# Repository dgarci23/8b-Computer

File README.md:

# 8-b Computer
8 bit Computer design based on Ben Eater's 8 Bit Computer Youtube series. Hardware implementation of the design, KiCad schematics and Verilog implementation.

The project consists of three parts:
- Hardware implementation of an 8 bit computer using TTL chips and breadboards following Ben Eater's design.
- Schematics and documentation for the hardware design in KiCad.
- FPGA implementation in an Altera DE2-115 using Verilog and Quartus.

# Hardware Design
Below is the final design of the breadboard implementation of the 8 bit Computer. 

### Modules
The breadboard implementation consists of:
- **Clock Module**: allows the user to work with an automatic clock with changeable frequency or a manual clock for debugging.
- **Memory Module**: 16 memory addresses of 8 bits each form the memory of the 8 bit computer. Both instructions and data are stored in the same memory. Manual memory programing is implemented.
- **Registers**: there are three registers implemented in the breadboard. Register A and B that hold data and the Instruction Register that holds the value of the current instruction.
- **ALU**: the ALU is able to implement addition and substraction of register A and B.
- **Program Counter**: the program counter keeps the value of the current instruction address.
- **Output Module**: the output module allows the user to see the results of the execution using 8 segment displays.
- **Control Unit**: using Flash Memories as "look-up tables" to keep the relationship between instructions and control signals, the Control Unit consists of the control signals that are sent into the different modules of the computer and the Flags Registers that allow for branch operations to work.

### ISA
The instruction set architecture for the computer is a custom made ISA for this specific implementation. 
It includes:
- A load immediate for Register A.
- A load and store functions for memory.
- Arithmetic functions add and substract.
- Jump instructions including simple jump, jump if zero and jump if carry.
- Output instruction to display on the 8 segment display.
- Halt instruction to stop execution.

### Power distribution and issues
Power distribution was a big challenge to make the computer work. Extensive connection between multiple ground and power lines was necessary to avoid high voltage differences across the computer that was creating bugs in the registers and the bus. Breadboard connections quality was also a problem, since some connections were not smooth and some chips disconnected from its breadboard creating bugs.

For the kiCad schematics of the implementation: [Click here](https://github.com/dgarci23/8b-Computer/blob/main/8'b%20Computer%20Schematics/Plot/8'b%20Computer.pdf)

# FPGA Implementation using Verilog
Using an Altera DE2-115 FPGA, I translated the breadboard implementation to a Verilog model and uploaded it to the FPGA using Quartus. Some minor changes were made from the Breadboard implementation, but the main functionality and ISA stayed the same. 

To improve program writing and loading into the FPGA, I developed a Serial terminal on PyGame to write and send programs to the FPGA via a USB-Serial cable and by implementing a program loader using Serial in the FPGA. 

The biggest challenges were to setup the serial communication in the FPGA in a way that it could detect where a program started. This was done by creating a "starting" sequence of two empty instructions (0x00) in a row, after that the actual program was fetched.

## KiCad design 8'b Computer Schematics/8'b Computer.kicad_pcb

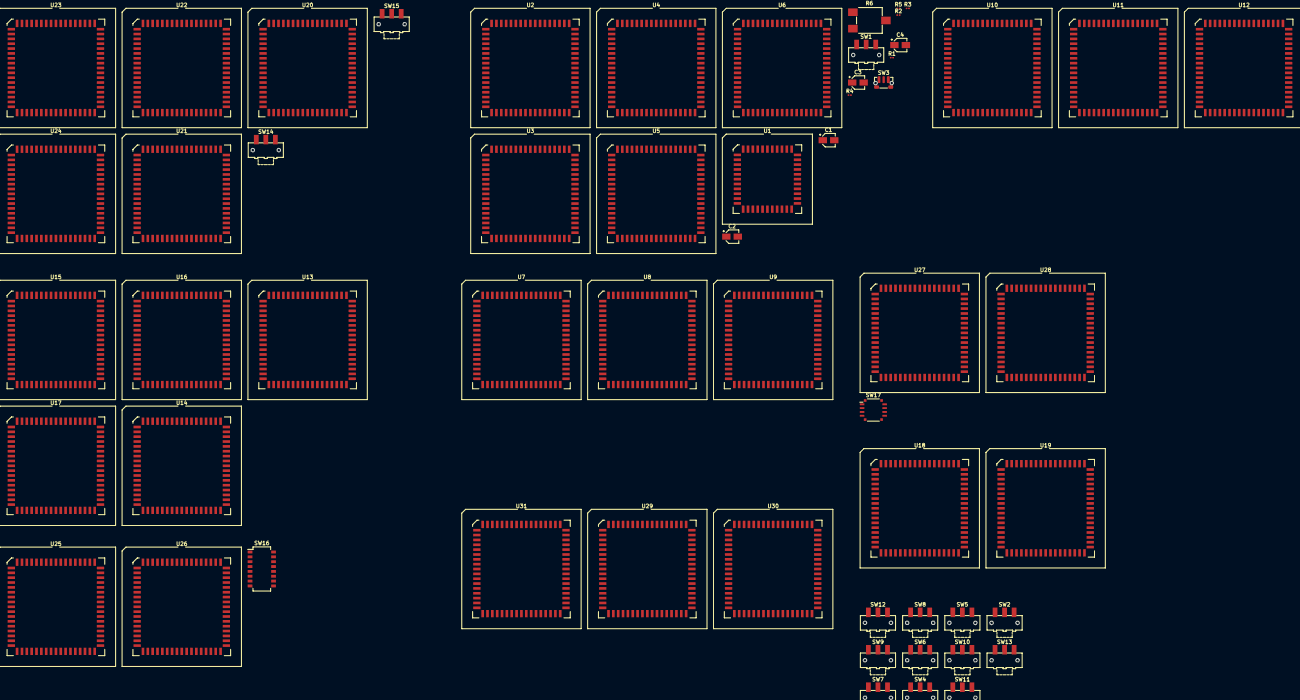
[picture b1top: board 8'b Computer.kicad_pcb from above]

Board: 2 copper layers, 58 parts (0 on the bottom side), 114 nets, no tracks yet.

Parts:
C1, C2, C4: 100p; CP_Elec_3x5.3
C3: 3.3u; CP_Elec_3x5.3
R1, R2, R3: 1k; R_0201_0603Metric
R4: 1M; R_0201_0603Metric
R5: 10k; R_0201_0603Metric
R6: 10k pot; Potentiometer_ACP_CA6-VSMD_Vertical
SW1, SW2, SW4, SW5, SW6, SW7, SW8, SW9, SW10, SW11, SW12, SW13, SW14: SW_SPDT; SW_SPDT_CK-JS102011SAQN
SW3: SW_Push; SW_Push_1P1T-MP_NO_Horizontal_Alps_SKRTLAE010
SW15: SW_Push; SW_SPDT_CK-JS102011SAQN
SW16: SW_DIP_x08; SW_DIP_SPSTx08_Slide_Omron_A6H-8101_W6.15mm_P1.27mm
SW17: SW_DIP_x04; SW_DIP_SPSTx04_Slide_Copal_CVS-04xB_W5.9mm_P1mm
U1: 74LS04; PLCC-44_SMD-Socket
U2, U5, U6: LM5550N; PLCC-68_SMD-Socket
U3: 74LS08; PLCC-68_SMD-Socket
U4: 74LS32; PLCC-68_SMD-Socket
U7, U10, U14, U18, U21, U23, U29: 74LS245; PLCC-68_SMD-Socket
U8, U9, U11, U12, U27, U30, U31: 74LS173; PLCC-68_SMD-Socket
U13, U16: 74LS86; PLCC-68_SMD-Socket
U15, U17: 74LS283; PLCC-68_SMD-Socket
U19: 74LS161; PLCC-68_SMD-Socket
U20: 74LS00; PLCC-68_SMD-Socket
U22, U25, U26, U28: 74LS157; PLCC-68_SMD-Socket
U24: AS6C62256; PLCC-68_SMD-Socket

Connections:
/ALU/SUB: SW10.2, U13.2, U13.5, U13.10, U13.13, U16.2, U16.5, U16.10, U16.13
/ALU/carry: U15.9, U17.7
/ALU/e0: U14.2, U15.4
/ALU/e1: U14.3, U15.1
/ALU/e2: U14.4, U15.13
/ALU/e3: U14.5, U15.10
/ALU/e4: U14.6, U17.4
/ALU/e5: U14.7, U17.1
/ALU/e6: U14.8, U17.13
/ALU/e7: U14.9, U17.10
/ALU/~EO: SW9.2, U14.19
/Clock/ASTABLE: U3.2, U6.3
/Clock/CoupleC: C1.1, U2.5
/Clock/HLT: SW2.2, U1.1
/Clock/MONOSTABLE: U3.4, U5.3
/Clock/SELECTOR: U1.3, U2.3, U3.5
/Instruction Register/inst4: U29.6, U31.3
/Instruction Register/inst5: U29.7, U31.4
/Instruction Register/inst6: U29.8, U31.5
/Instruction Register/inst7: U29.9, U31.6
/Instruction Register/~II: U30.9, U30.10, U31.9, U31.10
/Memory/Memory Address/MI: U27.9, U27.10
/Memory/Memory Address/manual0: SW17.1, U28.2
/Memory/Memory Address/manual1: SW17.2, U28.5
/Memory/Memory Address/manual2: SW17.3, U28.11
/Memory/Memory Address/manual3: SW17.4, U28.14
/Memory/Memory Address/mux_s: U22.1, U28.1
/Memory/Memory Values/manual0: SW16.8, U25.2
/Memory/Memory Values/manual1: SW16.7, U25.5
/Memory/Memory Values/manual2: SW16.6, U25.11
/Memory/Memory Values/manual3: SW16.5, U25.14
/Memory/Memory Values/manual4: SW16.4, U26.2
/Memory/Memory Values/manual5: SW16.3, U26.5
/Memory/Memory Values/manual6: SW16.2, U26.11
/Memory/Memory Values/manual7: SW16.1, U26.14
/Memory/Memory Values/mux_s: SW14.2, U25.1, U26.1
/Memory/WE: U20.2, U20.5
/Memory/inner0: U21.2, U23.2, U24.11
/Memory/inner1: U21.3, U23.3, U24.12
/Memory/inner2: U21.4, U23.4, U24.13
/Memory/inner3: U21.5, U23.5, U24.15
/Memory/inner4: U21.6, U23.6, U24.16
/Memory/inner5: U21.7, U23.7, U24.17
/Memory/inner6: U21.8, U23.8, U24.18
/Memory/inner7: U21.9, U23.9, U24.19
/Memory/~OE: U20.4, U21.19, U23.19, U24.22
/Program Counter/CE: SW12.2, U19.7, U19.10
/Program Counter/pc0: U18.14, U19.14
/Program Counter/pc1: U18.13, U19.13
/Program Counter/pc2: U18.12, U19.12
/Program Counter/pc3: U18.11, U19.11
/Program Counter/~CO: SW11.2, U18.19
/Program Counter/~J: SW13.2, U19.9
/RegisterA/a0: U7.2, U8.3
/RegisterA/a1: U7.3, U8.4
/RegisterA/a2: U7.4, U8.5
/RegisterA/a3: U7.5, U8.6
/RegisterA/a4: U7.6, U9.3
/RegisterA/a5: U7.7, U9.4
/RegisterA/a6: U7.8, U9.5
/RegisterA/a7: U7.9, U9.6
/RegisterA/~AI: SW4.2, U8.9, U8.10, U9.9, U9.10
/RegisterA/~AO: SW5.2, U7.19
/RegisterB/b0: U10.2, U11.3
/RegisterB/b1: U10.3, U11.4
/RegisterB/b2: U10.4, U11.5
/RegisterB/b3: U10.5, U11.6
/RegisterB/b4: U10.6, U12.3
/RegisterB/b5: U10.7, U12.4
/RegisterB/b6: U10.8, U12.5
/RegisterB/b7: U10.9, U12.6
/RegisterB/~BI: SW6.2, U11.9, U11.10, U12.9, U12.10
/RegisterB/~BO: SW7.2, U10.19
CLK: U3.8, U8.7, U9.7, U11.7, U12.7, U19.2, U20.1, U27.7, U30.7, U31.7
GND: C1.2, C2.1, C3.2, C4.1, SW1.2, SW2.1, SW3.1, SW4.1, SW5.1, SW6.1, SW7.1, SW8.1, SW9.1, SW10.1, SW11.1, SW12.1, SW13.1, SW14.1, SW15.1, SW16.9, SW16.10, SW16.11, SW16.12, SW16.13, SW16.14, SW16.15, SW16.16, SW17.5, SW17.6, SW17.7, SW17.8, U1.7, U2.1, U2.6, U2.7, U3.7, U4.7, U5.1, U6.1, U7.10, U8.1, U8.2, U8.8, U9.1, U9.2, U9.8, U10.10, U11.1, U11.2, U11.8, U12.1, U12.2, U12.8, U13.7, U14.10, U15.7, U15.8, U16.7, U17.8, U18.1, U18.2, U18.3, U18.4, U18.5, U18.10, U18.15, U18.16, U18.17, U18.18, U19.8, U20.7, U21.10, U22.8, U22.15, U23.10, U24.1, U24.2, U24.3, U24.4, U24.5, U24.6, U24.14, U24.20, U24.21, U24.23, U24.24, U24.25, U24.26, U25.8, U25.15, U26.8, U26.15, U27.1, U27.2, U27.8, U28.8, U28.15, U29.2, U29.3, U29.4, U29.5, U29.10, U30.1, U30.2, U30.8, U31.1, U31.2, U31.8
unnamed: C2.2, U5.5
unnamed: C3.1, R4.2, U5.6, U5.7
unnamed: C4.2, U6.5
unnamed: R1.2, SW1.1, U2.2
unnamed: R2.1, SW1.3, U2.4
unnamed: R3.2, SW3.2, U5.2
unnamed: R5.1, R6.2
unnamed: R5.2, U6.7
unnamed: R6.1, U6.2, U6.6
unnamed: SW15.2, U22.2
unnamed: U1.2, U3.10
unnamed: U1.4, U3.1
unnamed: U3.3, U4.2
unnamed: U3.6, U4.1
unnamed: U3.9, U4.3
unnamed: U13.3, U15.6
unnamed: U13.6, U15.2
unnamed: U13.8, U15.15
unnamed: U13.11, U15.11
unnamed: U16.3, U17.6
unnamed: U16.6, U17.2
unnamed: U16.8, U17.15
unnamed: U16.11, U17.11
unnamed: U20.3, U22.3
unnamed: U20.6, U21.1
unnamed: U27.3, U28.3
unnamed: U27.4, U28.6
unnamed: U27.5, U28.10
unnamed: U27.6, U28.13
PWR: R1.1, R2.2, R3.1, R4.1, SW2.3, SW4.3, SW5.3, SW6.3, SW7.3, SW8.3, SW9.3, SW10.3, SW11.3, SW12.3, SW13.3, SW14.3, U1.14, U2.8, U3.14, U4.14, U5.4, U5.8, U6.4, U6.8, U7.1, U7.20, U8.16, U9.16, U10.1, U10.20, U11.16, U12.16, U13.14, U14.1, U14.20, U15.16, U16.14, U17.16, U18.20, U19.16, U20.14, U21.20, U22.16, U23.1, U23.20, U24.28, U25.16, U26.16, U27.16, U28.16, U29.1, U29.20, U30.16, U31.16
bus0: U7.18, U8.14, U10.18, U11.14, U14.18, U23.18, U25.3, U29.18
bus1: U7.17, U8.13, U10.17, U11.13, U14.17, U23.17, U25.6, U29.17
bus2: U7.16, U8.12, U10.16, U11.12, U14.16, U23.16, U25.10, U29.16
bus3: U7.15, U8.11, U10.15, U11.11, U14.15, U23.15, U25.13, U29.15
bus4: U7.14, U9.14, U10.14, U12.14, U14.14, U18.6, U19.3, U23.14, U26.3, U27.14, U29.14
bus5: U7.13, U9.13, U10.13, U12.13, U14.13, U18.7, U19.4, U23.13, U26.6, U27.13, U29.13
bus6: U7.12, U9.12, U10.12, U12.12, U14.12, U18.8, U19.5, U23.12, U26.10, U27.12, U29.12
bus7: U7.11, U9.11, U10.11, U12.11, U14.11, U18.9, U19.6, U23.11, U26.13, U27.11, U29.11
~RST: SW8.2, U8.15, U9.15, U11.15, U12.15, U19.1, U27.15, U30.15, U31.15

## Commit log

2021-05-31 Create gitignore
2021-05-31 Update gitignore to include kiCad files
2021-05-31 Cleaning kiCad files
2021-05-31 Readded schematics
2021-06-01 Add comments to verilog files and finish design
2021-06-02 First working verilog implementation
2021-06-03 Manual write to memory implemented
2021-06-03 Stop HLT bug from stopping manual write
2021-06-05 Start to work on LCD implementation
2021-06-06 LCD Implementation - Display of Input Values for Memory
2021-06-14 uart program load
2021-06-23 Verilog changes
2021-07-11 Started working on documentation
2021-08-15 terminal documentation
2022-02-08 Various changes
